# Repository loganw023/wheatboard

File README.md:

# wheatboard
This is a custom-made devboard featuring a RP2040, I/O headers, a USB-C power supply, flash storage, crystal oscillator, and LEDs as indicators. This project was made to enhance my PCB skills, learn to use KiCad better, and qualify for Prototype, which I hope to attend. 

## Schematic 
Here is the schematic for the devboard. I tried to make it neat and organized, with labels for all major components of the devboard. Below is a screenshot: 
[i

## PCB
Here is the PCB for the devboard. The routing for the devboard took forever, since this was my first PCB project which lots of traces. I tried to organize all the components in a tight and effective manner. Below is a screenshot: 

## 3D-Model
Here is the 3D-Model for the devboard. Below is a screenshot of the top:
[
Below is a screenshot of the bottom: 

## BOM
I got the BOM from PLCPCB. One includes the parts, and the other includes the final cost.

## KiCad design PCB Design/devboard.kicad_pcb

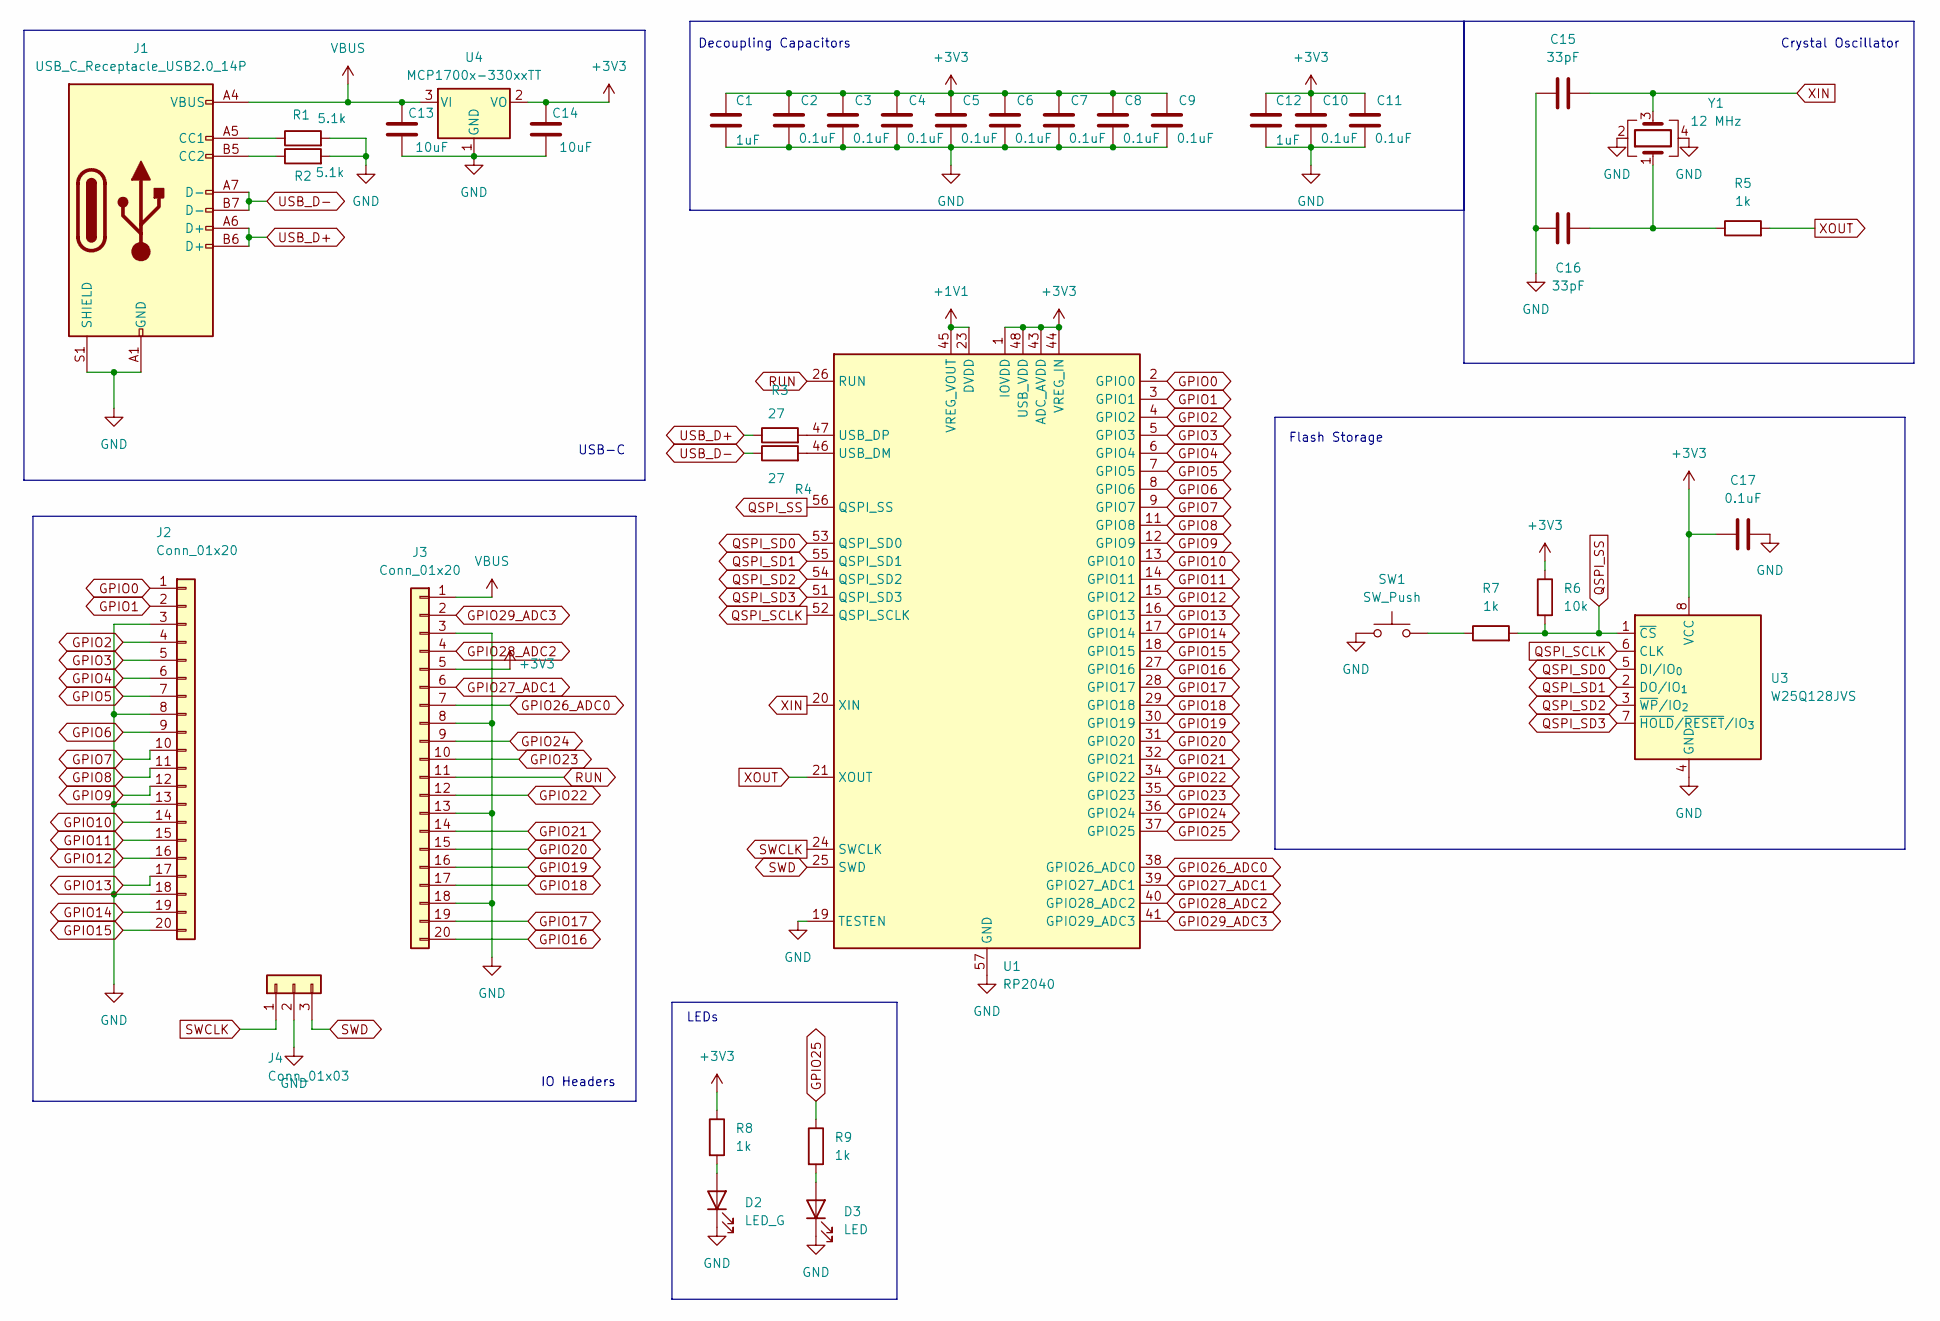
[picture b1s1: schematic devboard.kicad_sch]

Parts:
C1, C12: 1uF; C_0402_1005Metric
C2, C3, C4, C5, C6, C7, C8, C9, C10, C11, C17: 0.1uF; C_0402_1005Metric
C13, C14: 10uF; C_0603_1608Metric
C15, C16: 33pF; C_0402_1005Metric
D2: LED_G; LED_0603_1608Metric
D3: LED; LED_0603_1608Metric
J1: USB_C_Receptacle_USB2.0_14P; USB_C_Receptacle_HRO_TYPE-C-31-M-12
J2, J3: Conn_01x20; PinHeader_1x20_P2.54mm_Vertical
J4: Conn_01x03; PinHeader_1x03_P2.54mm_Vertical
R1, R2: 5.1k; R_0402_1005Metric
R3, R4: 27; R_0402_1005Metric
R5, R7, R8, R9: 1k; R_0402_1005Metric
R6: 10k; R_0402_1005Metric
SW1: SW_Push; SW_Push_SPST_NO_Alps_SKRK
U1: RP2040; QFN-56-1EP_7x7mm_P0.4mm_EP3.2x3.2mm
U3: W25Q128JVS; Winbond_USON-8-1EP_3x2mm_P0.5mm_EP0.2x1.6mm
U4: MCP1700x-330xxTT; SOT-23
Y1: 12 MHz; Crystal_SMD_3225-4Pin_3.2x2.5mm

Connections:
+1V1: U1.23 (DVDD), U1.45 (VREG_VOUT), U1.50 (DVDD)
+3V3: C1.1, C2.1, C3.1, C4.1, C5.1, C6.1, C7.1, C8.1, C9.1, C10.1, C11.1, C12.1, C14.1, C17.1, J3.5, R6.1, R8.1, U1.1 (IOVDD), U1.10 (IOVDD), U1.22 (IOVDD), U1.33 (IOVDD), U1.42 (IOVDD), U1.43 (ADC_AVDD), U1.44 (VREG_IN), U1.48 (USB_VDD), U1.49 (IOVDD), U3.8 (VCC), U4.2 (VO)
GND: C1.2, C2.2, C3.2, C4.2, C5.2, C6.2, C7.2, C8.2, C9.2, C10.2, C11.2, C12.2, C13.2, C14.2, C15.1, C16.1, C17.2, D2.1 (K), D3.1 (K), J1.A1 (GND), J1.A12 (GND), J1.B1 (GND), J1.B12 (GND), J1.S1 (SHIELD), J2.3, J2.8, J2.13, J2.18, J3.3, J3.8, J3.13, J3.18, J4.2, R1.2, R2.2, SW1.1, U1.19 (TESTEN), U1.57 (GND), U3.4 (GND), U4.1 (GND), Y1.2, Y1.4
GPIO0: J2.1, U1.2 (GPIO0)
GPIO1: J2.2, U1.3 (GPIO1)
GPIO2: J2.4, U1.4 (GPIO2)
GPIO3: J2.5, U1.5 (GPIO3)
GPIO4: J2.6, U1.6 (GPIO4)
GPIO5: J2.7, U1.7 (GPIO5)
GPIO6: J2.9, U1.8 (GPIO6)
GPIO7: J2.10, U1.9 (GPIO7)
GPIO8: J2.11, U1.11 (GPIO8)
GPIO9: J2.12, U1.12 (GPIO9)
GPIO10: J2.14, U1.13 (GPIO10)
GPIO11: J2.15, U1.14 (GPIO11)
GPIO12: J2.16, U1.15 (GPIO12)
GPIO13: J2.17, U1.16 (GPIO13)
GPIO14: J2.19, U1.17 (GPIO14)
GPIO15: J2.20, U1.18 (GPIO15)
GPIO16: J3.20, U1.27 (GPIO16)
GPIO17: J3.19, U1.28 (GPIO17)
GPIO18: J3.17, U1.29 (GPIO18)
GPIO19: J3.16, U1.30 (GPIO19)
GPIO20: J3.15, U1.31 (GPIO20)
GPIO21: J3.14, U1.32 (GPIO21)
GPIO22: J3.12, U1.34 (GPIO22)
GPIO23: J3.10, U1.35 (GPIO23)
GPIO24: J3.9, U1.36 (GPIO24)
GPIO25: R9.1, U1.37 (GPIO25)
GPIO26_ADC0: J3.7, U1.38 (GPIO26_ADC0)
GPIO27_ADC1: J3.6, U1.39 (GPIO27_ADC1)
GPIO28_ADC2: J3.4, U1.40 (GPIO28_ADC2)
GPIO29_ADC3: J3.2, U1.41 (GPIO29_ADC3)
unnamed: C16.2, R5.1, Y1.1
unnamed: D2.2 (A), R8.2
unnamed: D3.2 (A), R9.2
unnamed: J1.A5 (CC1), R1.1
unnamed: J1.B5 (CC2), R2.1
unnamed: R7.1, SW1.2
unnamed: R4.2, U1.46 (USB_DM)
unnamed: R3.2, U1.47 (USB_DP)
QSPI_SCLK: U1.52 (QSPI_SCLK), U3.6 (CLK)
QSPI_SD0: U1.53 (QSPI_SD0), U3.5 (DI/IO_{0})
QSPI_SD1: U1.55 (QSPI_SD1), U3.2 (DO/IO_{1})
QSPI_SD2: U1.54 (QSPI_SD2), U3.3 (~WP/IO_{2})
QSPI_SD3: U1.51 (QSPI_SD3), U3.7 (~HOLD/~RESET/IO_{3})
QSPI_SS: R6.2, R7.2, U1.56 (QSPI_SS), U3.1 (~CS)
RUN: J3.11, U1.26 (RUN)
SWCLK: J4.1, U1.24 (SWCLK)
SWD: J4.3, U1.25 (SWD)
USB_D+: J1.A6 (D+), J1.B6 (D+), R3.1
USB_D-: J1.A7 (D-), J1.B7 (D-), R4.1
VBUS: C13.1, J1.A4 (VBUS), J1.A9 (VBUS), J1.B4 (VBUS), J1.B9 (VBUS), J3.1, U4.3 (VI)
XIN: C15.2, U1.20 (XIN), Y1.3
XOUT: R5.2, U1.21 (XOUT)

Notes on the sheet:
Flash Storage
USB-C
Decoupling Capacitors
Crystal Oscillator
LEDs
IO Headers

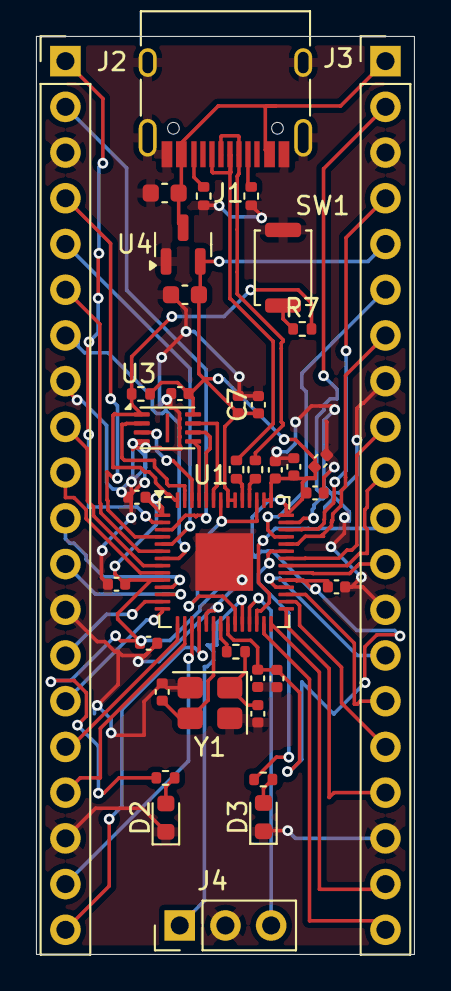
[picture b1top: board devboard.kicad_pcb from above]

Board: 2 copper layers, 21.0 x 51.0 mm, 37 parts (0 on the bottom side), 55 nets.

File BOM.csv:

Id,Designator,Footprint,Quantity,Comment,Supplier and ref
1,"R5,R8,R9,R7",R_0402_1005Metric,4,1k,
2,"R4,R3",R_0402_1005Metric,2,27,
3,U4,SOT-23,1,MCP1700x-330xxTT,
4,SW1,SW_Push_SPST_NO_Alps_SKRK,1,SW_Push,
5,"C10,C9,C8,C6,C17,C3,C11,C2,C4,C7,C5",C_0402_1005Metric,11,0.1uF,
6,D2,LED_0603_1608Metric,1,LED_G,
7,"C16,C15",C_0402_1005Metric,2,33pF,
8,U1,QFN-56-1EP_7x7mm_P0.4mm_EP3.2x3.2mm,1,RP2040,
9,"J2,J3",PinHeader_1x20_P2.54mm_Vertical,2,Conn_01x20,
10,R6,R_0402_1005Metric,1,10k,
11,"C1,C12",C_0402_1005Metric,2,1uF,
12,"R1,R2",R_0402_1005Metric,2,5.1k,
13,J1,USB_C_Receptacle_HRO_TYPE-C-31-M-12,1,USB_C_Receptacle_USB2.0_14P,
14,Y1,Crystal_SMD_3225-4Pin_3.2x2.5mm,1,12 MHz,
15,"C13,C14",C_0603_1608Metric,2,10uF,
16,D3,LED_0603_1608Metric,1,LED,
17,U3,Winbond_USON-8-1EP_3x2mm_P0.5mm_EP0.2x1.6mm,1,W25Q128JVS,
18,J4,PinHeader_1x03_P2.54mm_Vertical,1,Conn_01x03,

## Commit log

2025-12-02 Added all files for project
2025-12-02 Fixed README
2025-12-02 Finalized
2025-12-02 Fixed BOM issue.
2025-12-06 Organized
2025-12-06 Fixed
2025-12-06 Hopefully this works
2025-12-06 Fixed readme...
